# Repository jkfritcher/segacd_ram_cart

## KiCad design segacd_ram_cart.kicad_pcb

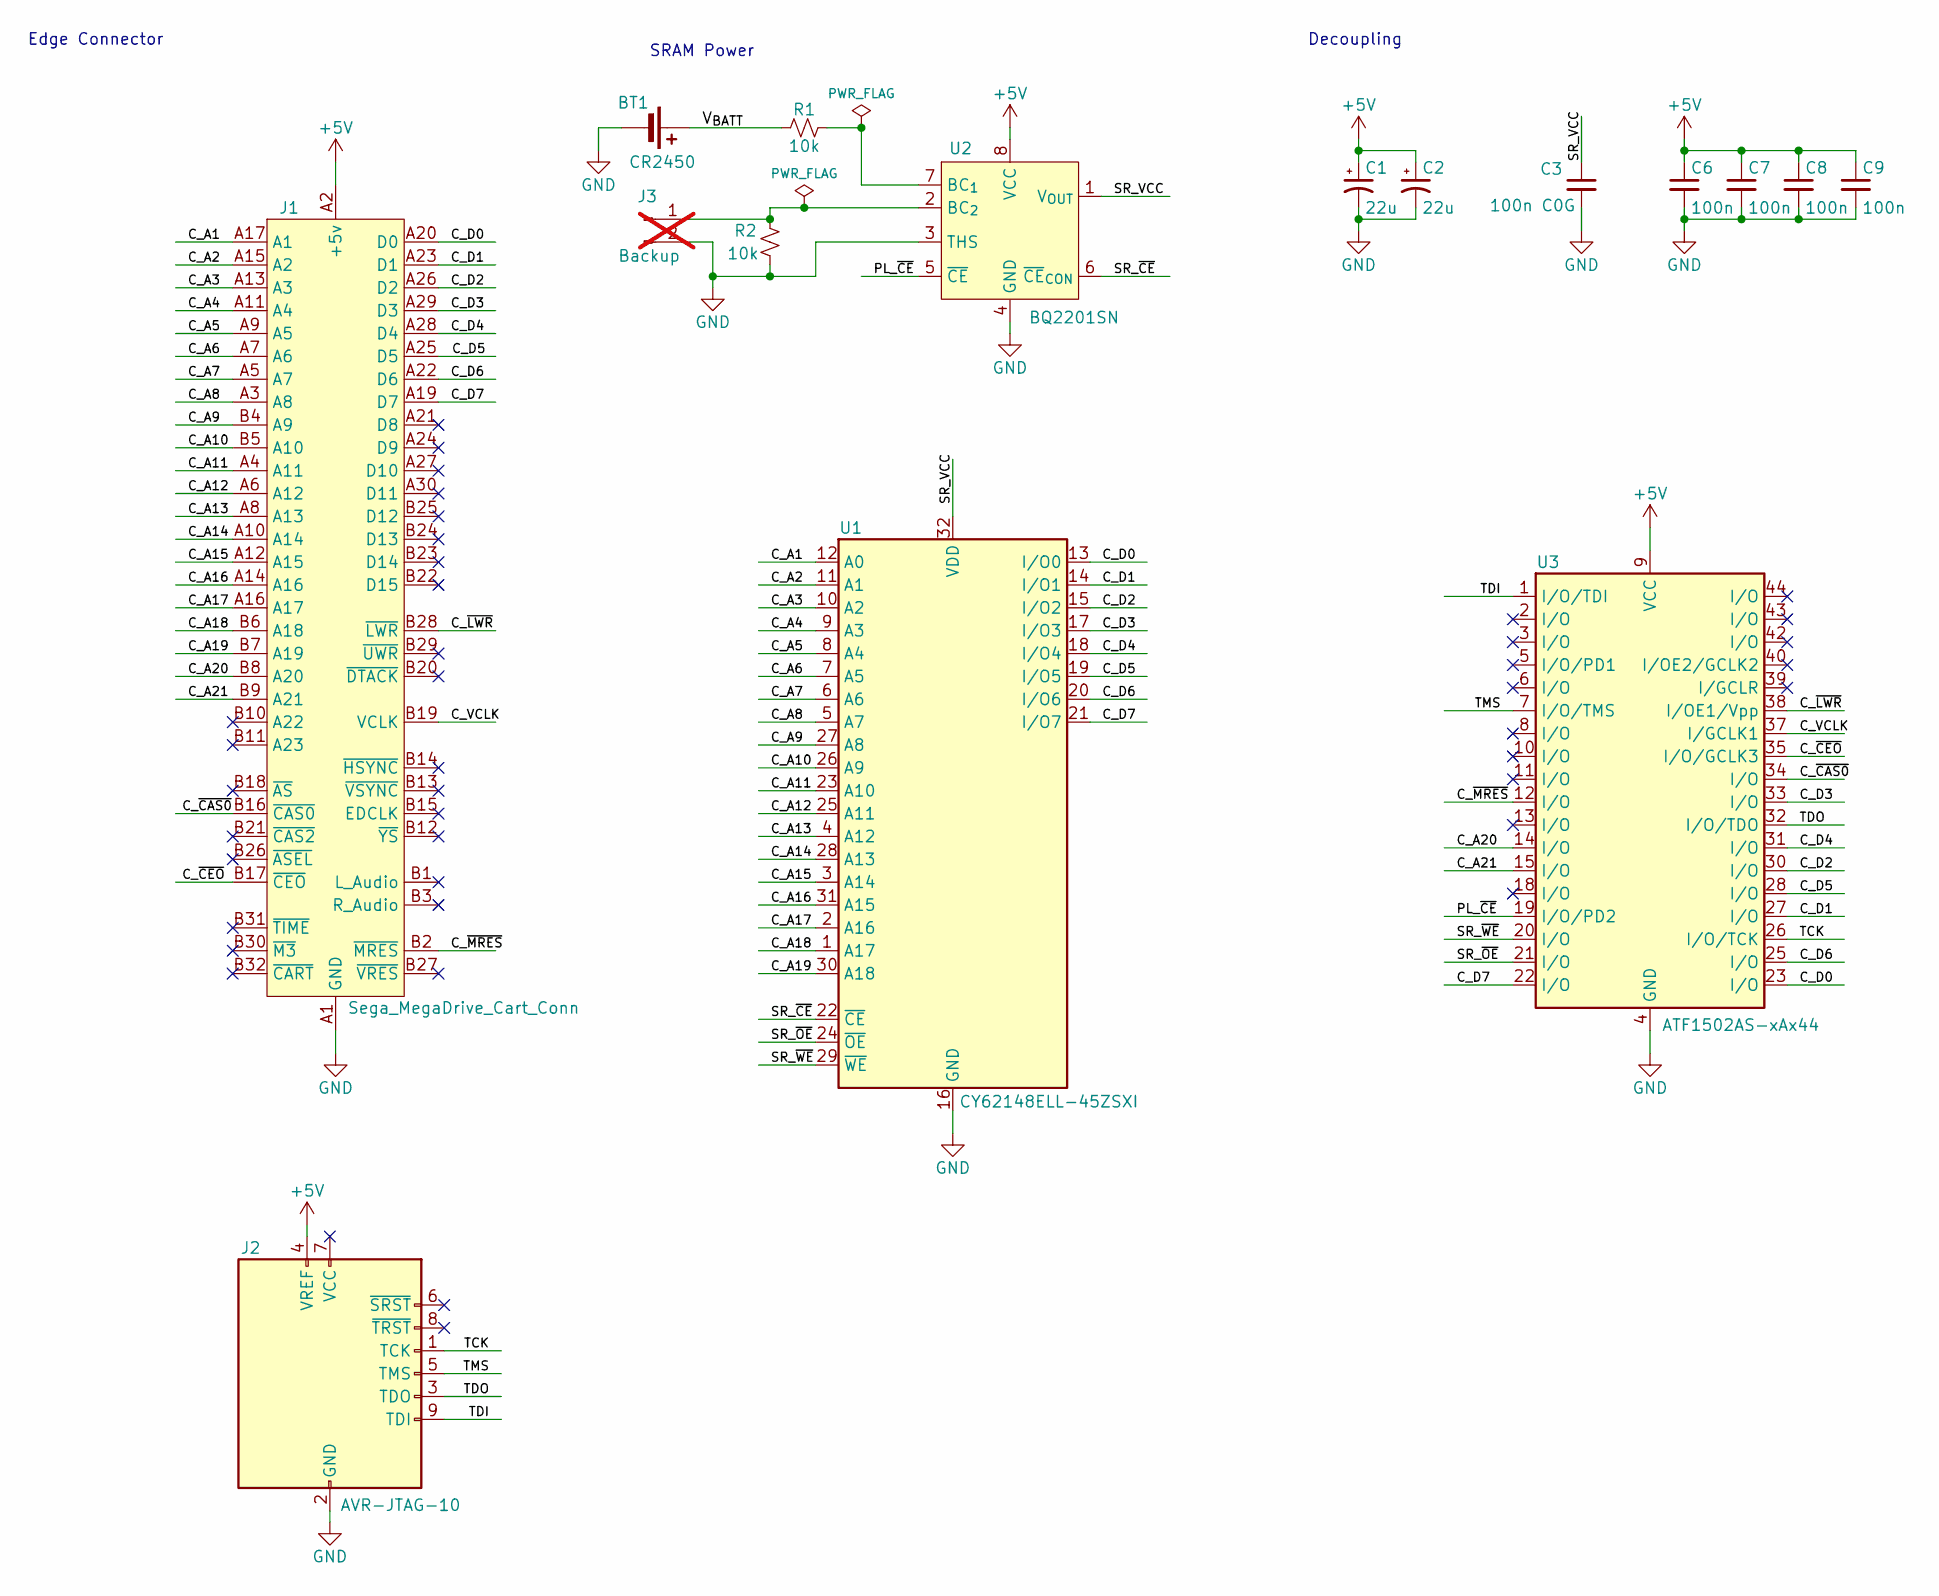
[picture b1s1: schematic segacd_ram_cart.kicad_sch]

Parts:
BT1: CR2450; BatteryHolder_Keystone_3008_1x2450
C1, C2: 22u; C_Elec_4x5.4
C3: 100n C0G; C_0603_1608Metric
C6, C7, C8, C9: 100n; C_0603_1608Metric
J1: Sega_MegaDrive_Cart_Conn; 2x32_P2.54mm_Edge
J2: AVR-JTAG-10; Tag-Connect_TC2050-IDC-FP_2x05_P1.27mm_Vertical
J3: Backup; PinHeader_1x02_P2.54mm_Vertical; not fitted
R1, R2: 10k; R_0603_1608Metric
U1: CY62148ELL-45ZSXI; TSOP-II-32_21.0x10.2mm_P1.27mm
U2: BQ2201SN; SOIC-8_3.9x4.9mm_P1.27mm
U3: ATF1502AS-xAx44; TQFP-44_10x10mm_P0.8mm

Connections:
+5V: C1.1, C2.1, C6.1, C7.1, C8.1, C9.1, J1.A2 (+5v), J1.A31 (+5v), J2.4 (VREF), U2.8 (VCC), U3.9 (VCC), U3.17 (VCC), U3.29 (VCC), U3.41 (VCC)
/C_A1: J1.A17 (A1), U1.12 (A0)
/C_A2: J1.A15 (A2), U1.11 (A1)
/C_A3: J1.A13 (A3), U1.10 (A2)
/C_A4: J1.A11 (A4), U1.9 (A3)
/C_A5: J1.A9 (A5), U1.8 (A4)
/C_A6: J1.A7 (A6), U1.7 (A5)
/C_A7: J1.A5 (A7), U1.6 (A6)
/C_A8: J1.A3 (A8), U1.5 (A7)
/C_A9: J1.B4 (A9), U1.27 (A8)
/C_A10: J1.B5 (A10), U1.26 (A9)
/C_A11: J1.A4 (A11), U1.23 (A10)
/C_A12: J1.A6 (A12), U1.25 (A11)
/C_A13: J1.A8 (A13), U1.4 (A12)
/C_A14: J1.A10 (A14), U1.28 (A13)
/C_A15: J1.A12 (A15), U1.3 (A14)
/C_A16: J1.A14 (A16), U1.31 (A15)
/C_A17: J1.A16 (A17), U1.2 (A16)
/C_A18: J1.B6 (A18), U1.1 (A17)
/C_A19: J1.B7 (A19), U1.30 (A18)
/C_A20: J1.B8 (A20), U3.14 (I/O)
/C_A21: J1.B9 (A21), U3.15 (I/O)
/C_D0: J1.A20 (D0), U1.13 (I/O0), U3.23 (I/O)
/C_D1: J1.A23 (D1), U1.14 (I/O1), U3.27 (I/O)
/C_D2: J1.A26 (D2), U1.15 (I/O2), U3.30 (I/O)
/C_D3: J1.A29 (D3), U1.17 (I/O3), U3.33 (I/O)
/C_D4: J1.A28 (D4), U1.18 (I/O4), U3.31 (I/O)
/C_D5: J1.A25 (D5), U1.19 (I/O5), U3.28 (I/O)
/C_D6: J1.A22 (D6), U1.20 (I/O6), U3.25 (I/O)
/C_D7: J1.A19 (D7), U1.21 (I/O7), U3.22 (I/O)
/C_VCLK: J1.B19 (VCLK), U3.37 (I/GCLK1)
/C_~CAS0: J1.B16 (~CAS0), U3.34 (I/O)
/C_~CEO: J1.B17 (~CEO), U3.35 (I/O/GCLK3)
/C_~LWR: J1.B28 (~LWR), U3.38 (I/OE1/Vpp)
/C_~MRES: J1.B2 (~MRES), U3.12 (I/O)
/PL_~CE: U2.5 (~CE), U3.19 (I/O/PD2)
/SR_VCC: C3.1, U1.32 (VDD), U2.1 (V_{OUT})
/SR_~CE: U1.22 (~CE), U2.6 (~CE_{CON})
/SR_~OE: U1.24 (~OE), U3.21 (I/O)
/SR_~WE: U1.29 (~WE), U3.20 (I/O)
/TCK: J2.1 (TCK), U3.26 (I/O/TCK)
/TDI: J2.9 (TDI), U3.1 (I/O/TDI)
/TDO: J2.3 (TDO), U3.32 (I/O/TDO)
/TMS: J2.5 (TMS), U3.7 (I/O/TMS)
/V_{BATT}: BT1.1 (+), R1.1
GND: BT1.2 (-), C1.2, C2.2, C3.2, C6.2, C7.2, C8.2, C9.2, J1.A1 (GND), J1.A18 (GND), J1.A32 (GND), J2.2 (GND), J2.10 (GND), J3.2, R2.1, U1.16 (GND), U2.3 (THS), U2.4 (GND), U3.4 (GND), U3.16 (GND), U3.24 (GND), U3.36 (GND)
unnamed: J3.1, R2.2, U2.2 (BC_{2})
unnamed: R1.2, U2.7 (BC_{1})

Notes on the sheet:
Decoupling
SRAM Power
Edge Connector

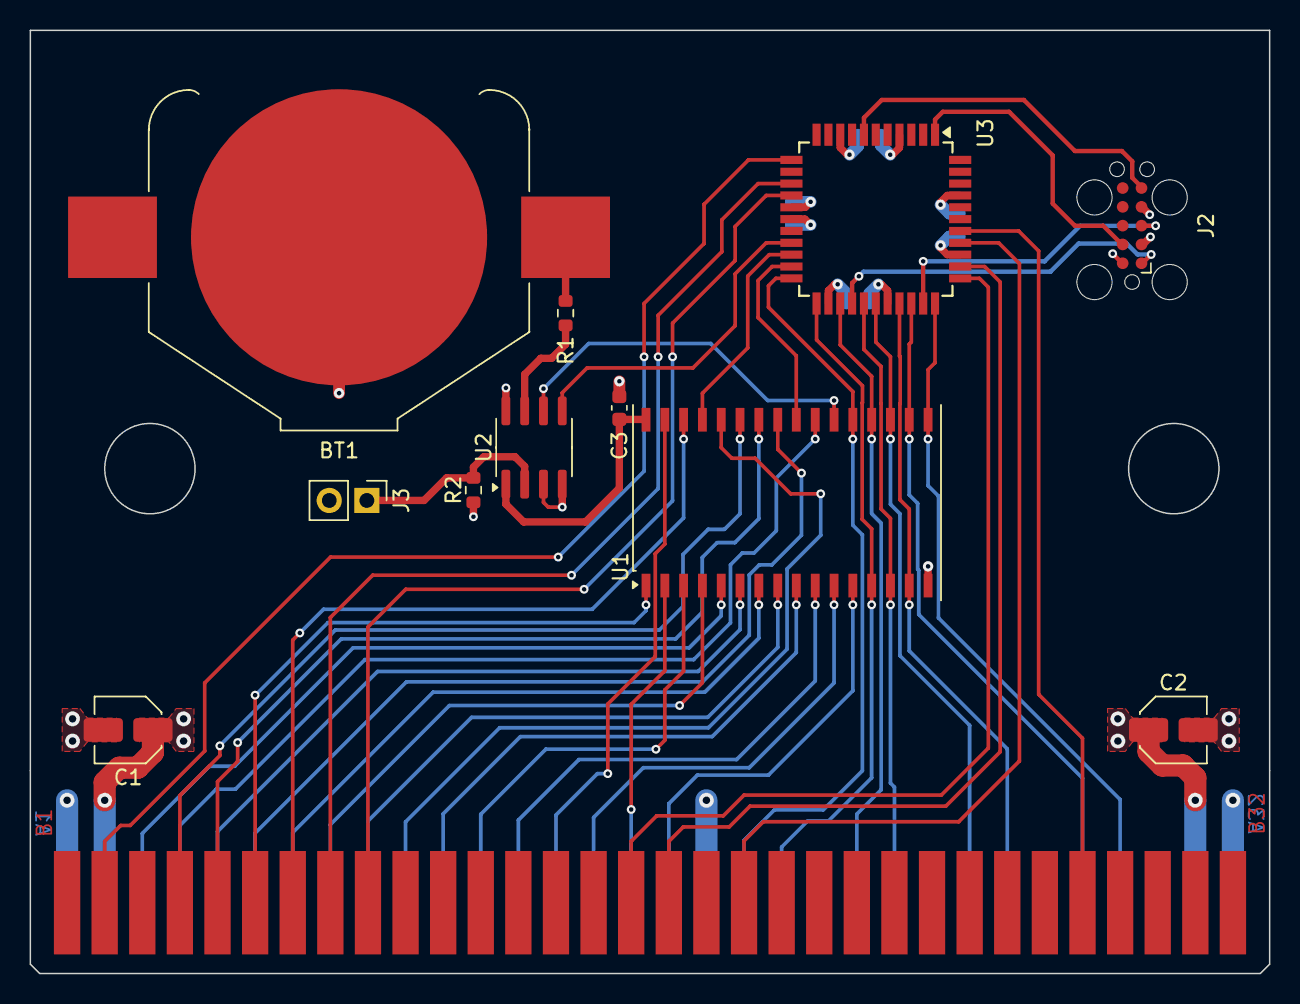
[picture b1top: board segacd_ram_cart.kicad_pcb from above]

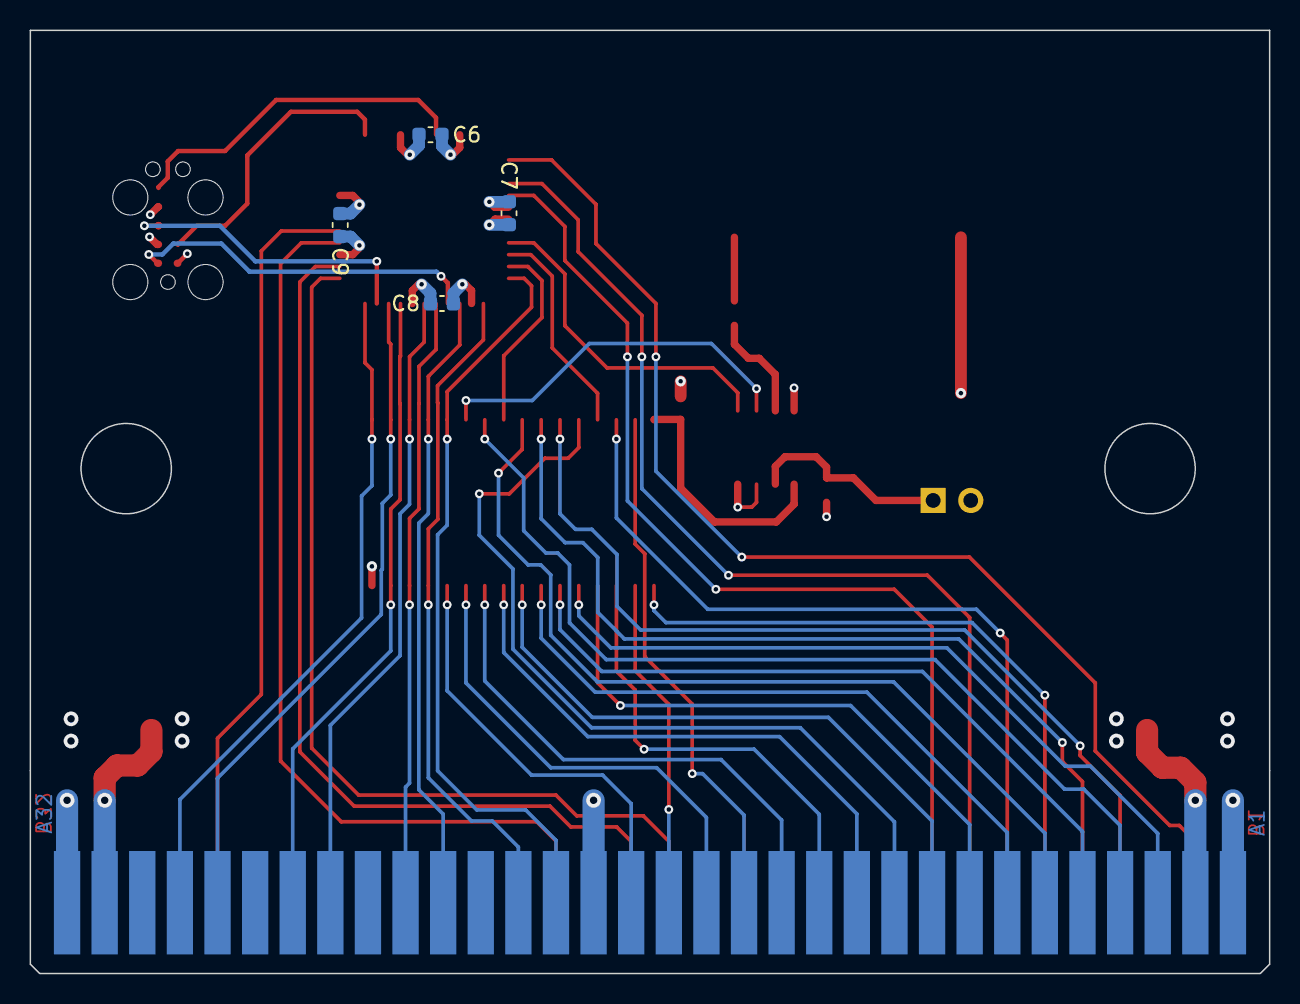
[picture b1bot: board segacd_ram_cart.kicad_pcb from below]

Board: 4 copper layers, 83.7 x 63.7 mm, 16 parts (4 on the bottom side), 48 nets.

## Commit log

2024-08-04 Add LICENSE
2024-08-04 Changed layout and updated symbols/footprints
    * Changed the layout of components to allow for shrinking the board.
    * Imported custom symbols and footprints into project library.
    * Updated symbols and footprints to satisfy ERC/DRC checks.
2024-08-04 Dev snapshot
